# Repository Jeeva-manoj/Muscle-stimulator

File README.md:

# Muscle-stimulator
This circuit design can be used for pain relief and physiotherapy
These are EAGLE documents and the gerber files are also included

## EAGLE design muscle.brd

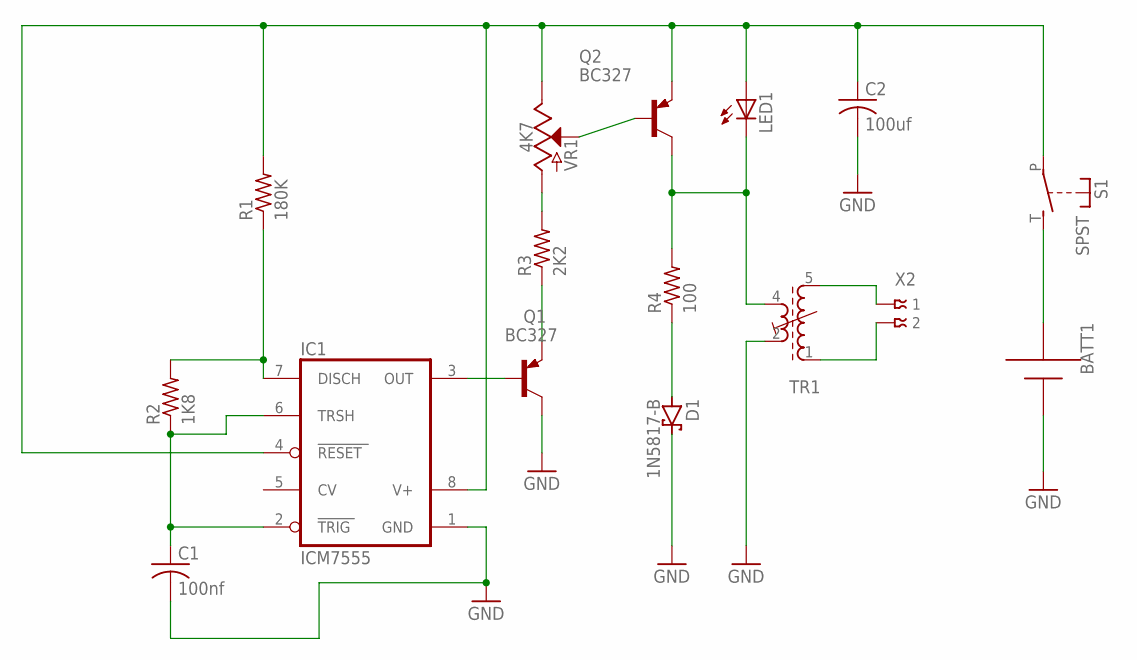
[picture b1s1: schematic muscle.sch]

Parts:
BATT1: AAA; 12BH412; MPN BX0034
C1: 100nf; C025-024X044; MPN 12065C104KAT2A
C2: 100uf; C025-024X044; MPN C1210C107M9PACTU
D1: 1N5817-B; DO41-7.6; MPN 1N5817G
IC1: ICM7555; DIL08; MPN ICM7555IPAZ
LED1: LED3MM; MPN L-424IDT
Q1, Q2: BC327; TO92
R1: 180K; 0204V
R2: 1K8; 0204V
R3: 2K2; 0204V
R4: 100; 0204V
S1: SPST; JUDCOSPST
TR1: 71-4-1524; 71-5
VR1: 4K7; SLIDER-SMALL
X2: 009177002

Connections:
GND: BATT1.+, C1.2, C2.2, D1.C, IC1.1 (GND), Q1.3 (C), TR1.2 (A2)
unnamed: IC1.3 (OUT), Q1.2 (B)
unnamed: Q1.1 (E), R3.1
unnamed: R3.2, VR1.BOTTOM (A)
unnamed: Q2.2 (B), VR1.WIPER (S)
unnamed: IC1.7 (DISCH), R1.1, R2.2
unnamed: C1.1, IC1.2 (TRIG), IC1.6 (TRSH), R2.1
unnamed: C2.1, IC1.4 (RESET), IC1.8 (V+), LED1.A, Q2.1 (E), R1.2, S1.P, VR1.TOP (E)
unnamed: D1.A, R4.1
unnamed: BATT1.-, S1.T (S)
unnamed: LED1.K (C), Q2.3 (C), R4.2, TR1.4 (E2)
unnamed: TR1.5 (E1), X2.1
unnamed: TR1.1 (A1), X2.2

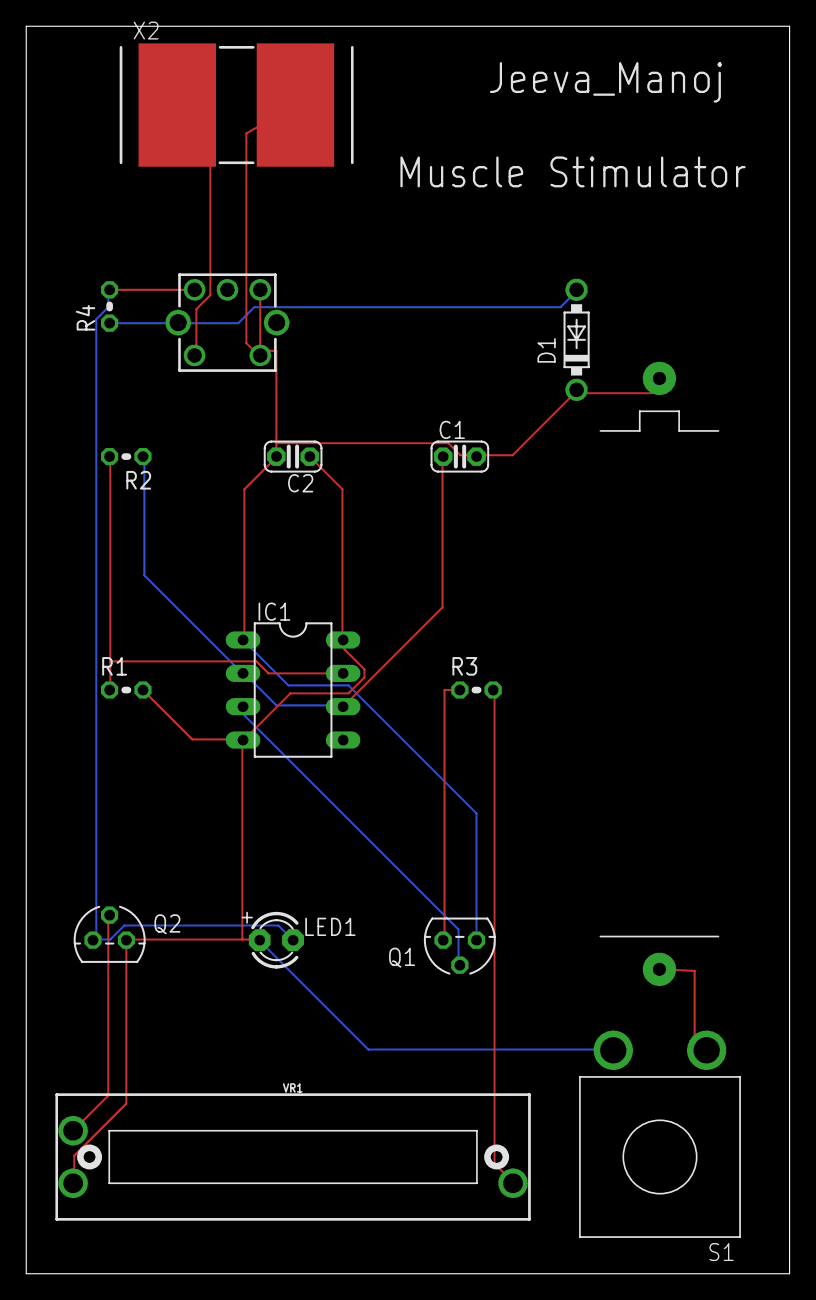
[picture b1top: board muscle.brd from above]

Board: 2 copper layers, 58.1 x 95.0 mm, 16 parts (0 on the bottom side), 13 nets.

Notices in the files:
parts and their libraries:
SparkFun-Resistors: Licensing: Creative Commons ShareAlike 4.0 International - https://creativecommons.org/licenses/by-sa/4.0
